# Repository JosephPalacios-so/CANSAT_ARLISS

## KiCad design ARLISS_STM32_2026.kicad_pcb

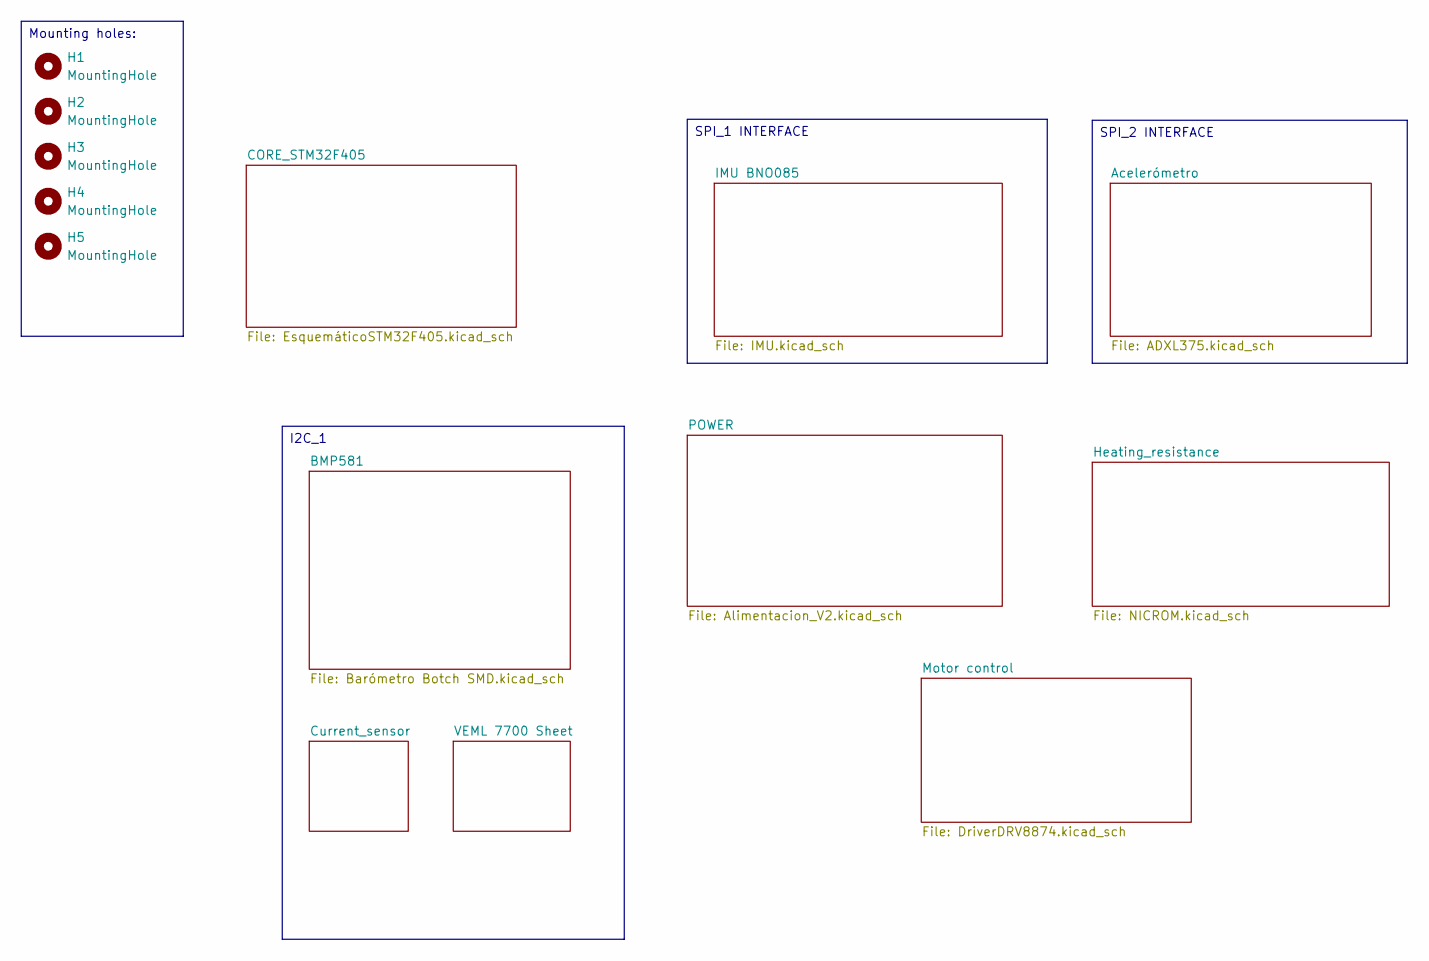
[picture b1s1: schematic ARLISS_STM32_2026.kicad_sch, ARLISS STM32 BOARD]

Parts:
H1, H2, H3, H4, H5: MountingHole; MountingHole_3.2mm_M3_ISO14580_Pad

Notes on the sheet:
SPI_1 INTERFACE
Mounting holes:
SPI_2 INTERFACE
I2C_1

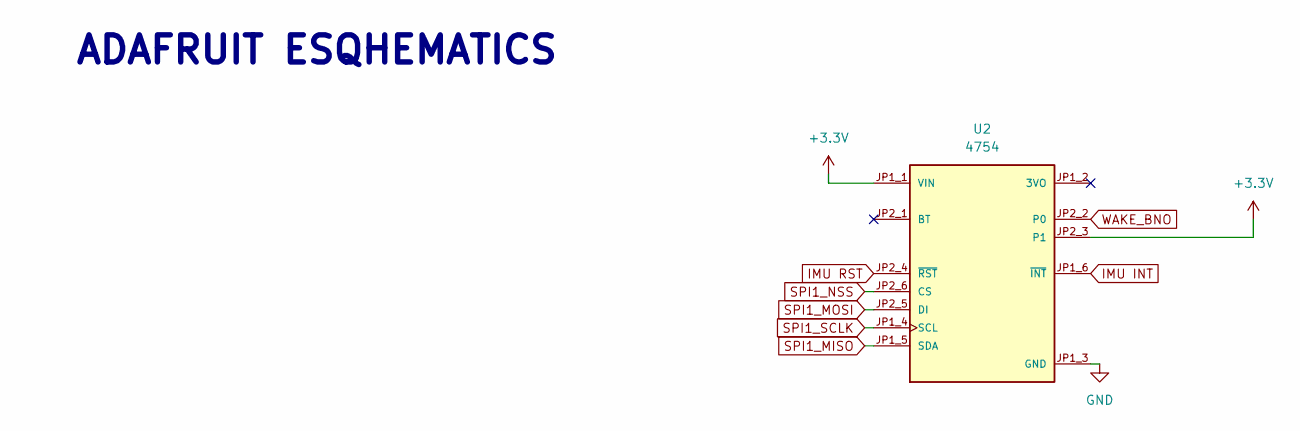
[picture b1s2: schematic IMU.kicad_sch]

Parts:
U2: 4754; MODULE_4754; PARTREV 2021-03-16

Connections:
GND: U2.JP1_3 (GND); also elsewhere on the board
IMU INT: U2.JP1_6 (~INT); also elsewhere on the board
IMU RST: U2.JP2_4 (~RST); also elsewhere on the board
SPI1_MISO: U2.JP1_5 (SDA); also elsewhere on the board
SPI1_MOSI: U2.JP2_5 (DI); also elsewhere on the board
SPI1_NSS: U2.JP2_6 (CS); also elsewhere on the board
SPI1_SCLK: U2.JP1_4 (SCL); also elsewhere on the board
WAKE_BNO: U2.JP2_2 (P0); also elsewhere on the board

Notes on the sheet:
ADAFRUIT ESQHEMATICS

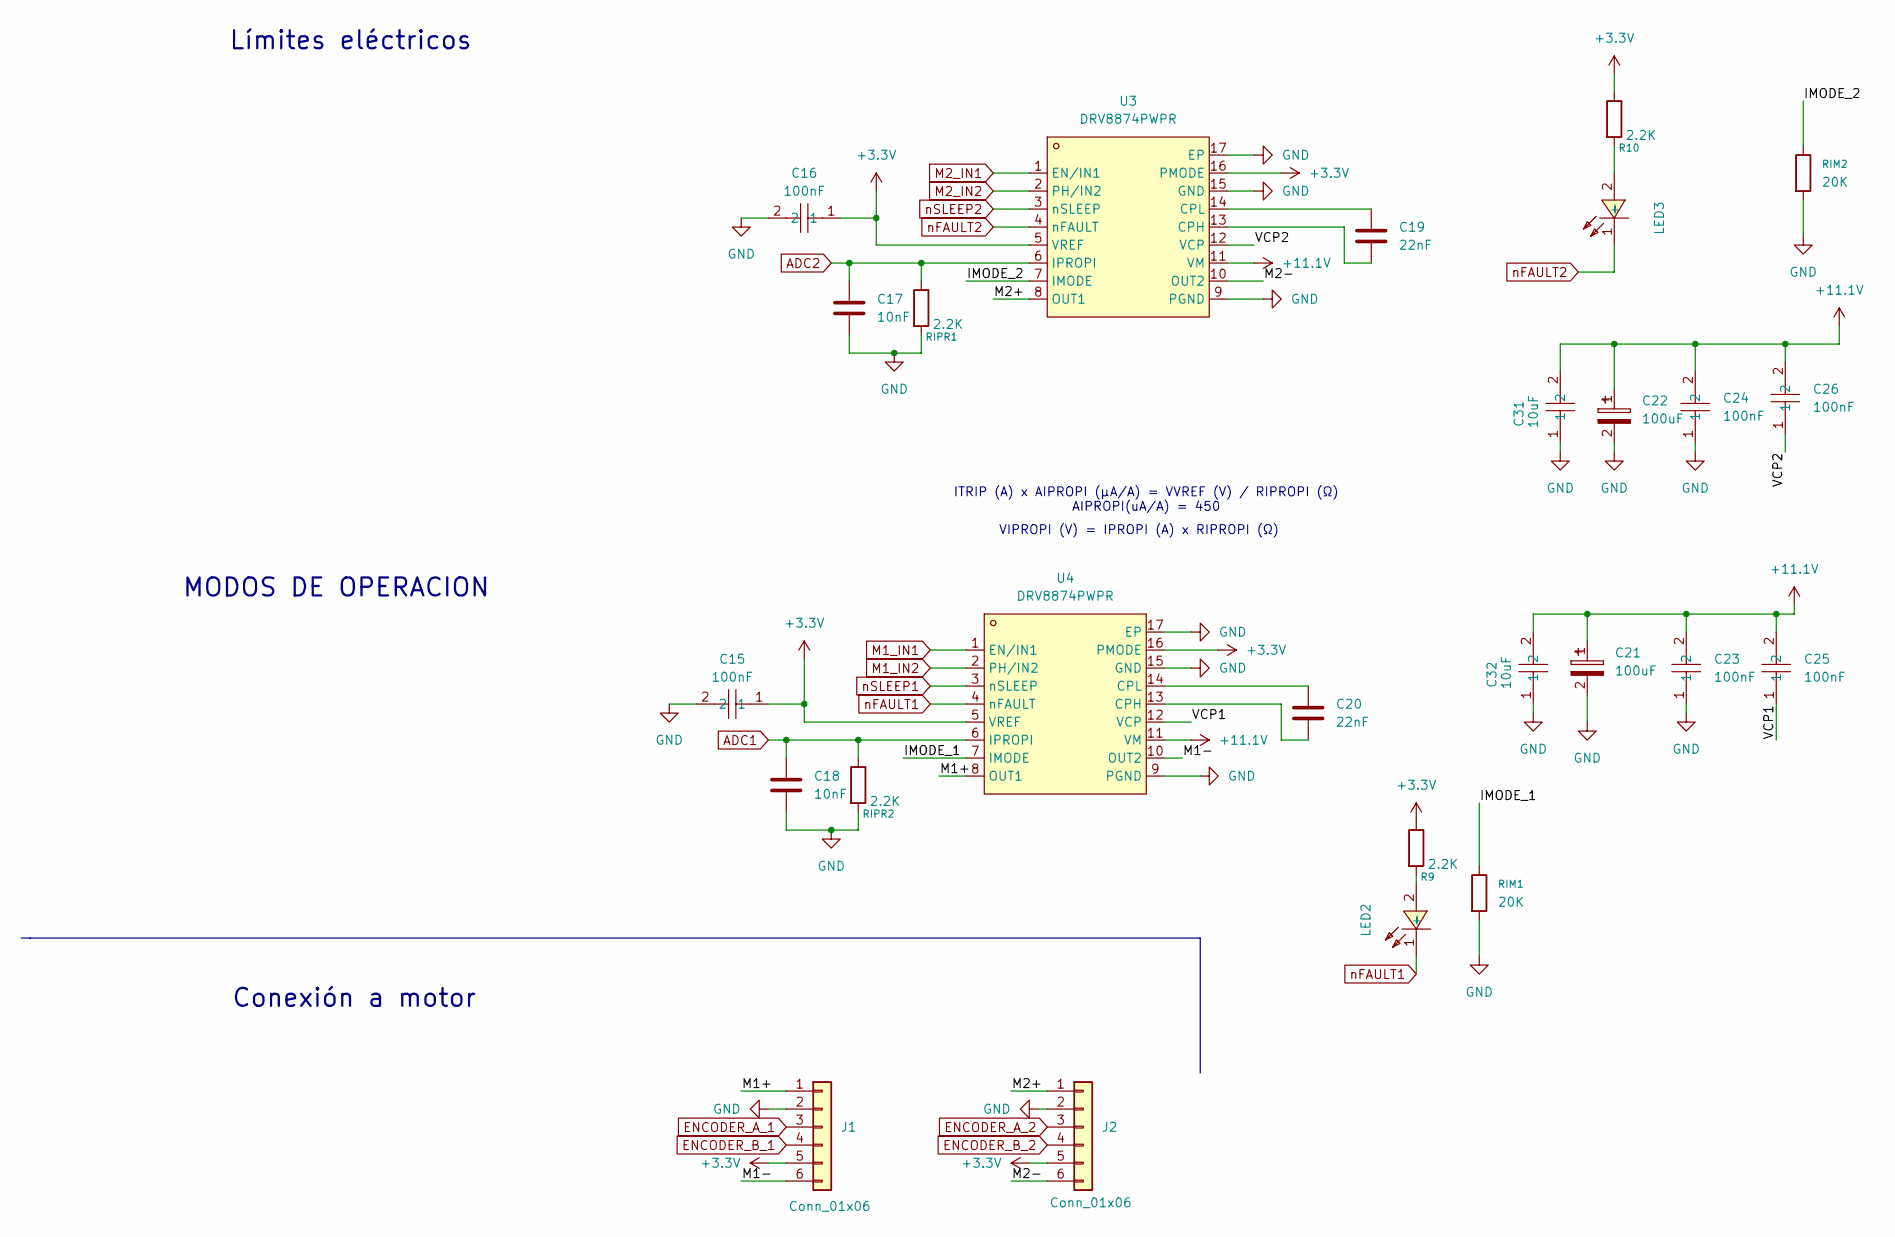
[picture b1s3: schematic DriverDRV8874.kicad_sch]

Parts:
C15, C16, C23, C24, C25, C26: 100nF; C_0603_1608Metric_Pad1.08x0.95mm_HandSolder; MPN TCC0402X7R104J500AT; LCSC Part C282518
C17, C18: 10nF; C_0603_1608Metric_Pad1.08x0.95mm_HandSolder; LCSC C85973
C19, C20: 22nF; C_0603_1608Metric_Pad1.08x0.95mm_HandSolder; LCSC C541460
C21, C22: 100uF; CAP-SMD_BD6.3-L6.6-W6.6-FD; MPN UCM1H101MCL1GS; LCSC Part C729685
C31, C32: 10uF; C_0805_2012Metric_Pad1.18x1.45mm_HandSolder; MPN CL21B106KAYQNNE; LCSC Part C3039694
J1, J2: Conn_01x06; JST_XH_B6B-XH-A_1x06_P2.50mm_Vertical
LED2, LED3: D-R060306L3-KS2; D_0603_1608Metric_Pad1.05x0.95mm_HandSolder; MPN D-060306R1/SS2/L; LCSC Part C118330
R9, R10: 2.2K; R_0603_1608Metric_Pad0.98x0.95mm_HandSolder; LCSC C125931
RIM1, RIM2: 20K; R_0603_1608Metric_Pad0.98x0.95mm_HandSolder; LCSC C7274188
RIPR1, RIPR2: 2.2K; R_0603_1608Metric_Pad0.98x0.95mm_HandSolder; LCSC C125931
U3, U4: DRV8874PWPR; HTSSOP-16_L5.0-W4.4-P0.65-LS6.4-BL-EP; MPN DRV8874PWPR; LCSC Part C1855818

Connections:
+11.1V: C21.1, C22.1, C23.2, C24.2, C25.2, C26.2, C31.2, C32.2, U3.11 (VM), U4.11 (VM); also elsewhere on the board
/Motor control/IMODE_1: RIM1.1, U4.7 (IMODE)
/Motor control/IMODE_2: RIM2.1, U3.7 (IMODE)
/Motor control/M1+: J1.1, U4.8 (OUT1)
/Motor control/M1-: J1.6, U4.10 (OUT2)
/Motor control/M2+: J2.1, U3.8 (OUT1)
/Motor control/M2-: J2.6, U3.10 (OUT2)
/Motor control/VCP1: C25.1, U4.12 (VCP)
/Motor control/VCP2: C26.1, U3.12 (VCP)
ADC1: C18.1, RIPR2.1, U4.6 (IPROPI); also elsewhere on the board
ADC2: C17.1, RIPR1.1, U3.6 (IPROPI); also elsewhere on the board
ENCODER_A_1: J1.3; also elsewhere on the board
ENCODER_A_2: J2.3; also elsewhere on the board
ENCODER_B_1: J1.4; also elsewhere on the board
ENCODER_B_2: J2.4; also elsewhere on the board
GND: C15.2, C16.2, C17.2, C18.2, C21.2, C22.2, C23.1, C24.1, C31.1, C32.1, J1.2, J2.2, RIM1.2, RIM2.2, RIPR1.2, RIPR2.2, U3.9 (PGND), U3.15 (GND), U3.17 (EP), U4.9 (PGND), U4.15 (GND), U4.17 (EP); also elsewhere on the board
M1_IN1: U4.1 (EN/IN1); also elsewhere on the board
M1_IN2: U4.2 (PH/IN2); also elsewhere on the board
M2_IN1: U3.1 (EN/IN1); also elsewhere on the board
M2_IN2: U3.2 (PH/IN2); also elsewhere on the board
unnamed: LED2.2 (+), R9.2
unnamed: LED3.2 (+), R10.2
unnamed: C19.2, U3.13 (CPH)
unnamed: C19.1, U3.14 (CPL)
unnamed: C20.2, U4.13 (CPH)
unnamed: C20.1, U4.14 (CPL)
nFAULT1: LED2.1 (-), U4.4 (nFAULT); also elsewhere on the board
nFAULT2: LED3.1 (-), U3.4 (nFAULT); also elsewhere on the board
nSLEEP1: U4.3 (nSLEEP); also elsewhere on the board
nSLEEP2: U3.3 (nSLEEP); also elsewhere on the board

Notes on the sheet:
Límites eléctricos
MODOS DE OPERACION
VIPROPI (V) = IPROPI (A) x RIPROPI (Ω)
Conexión a motor
ITRIP (A) x AIPROPI (μA/A) = VVREF (V) / RIPROPI (Ω) AIPROPI(uA/A) = 450

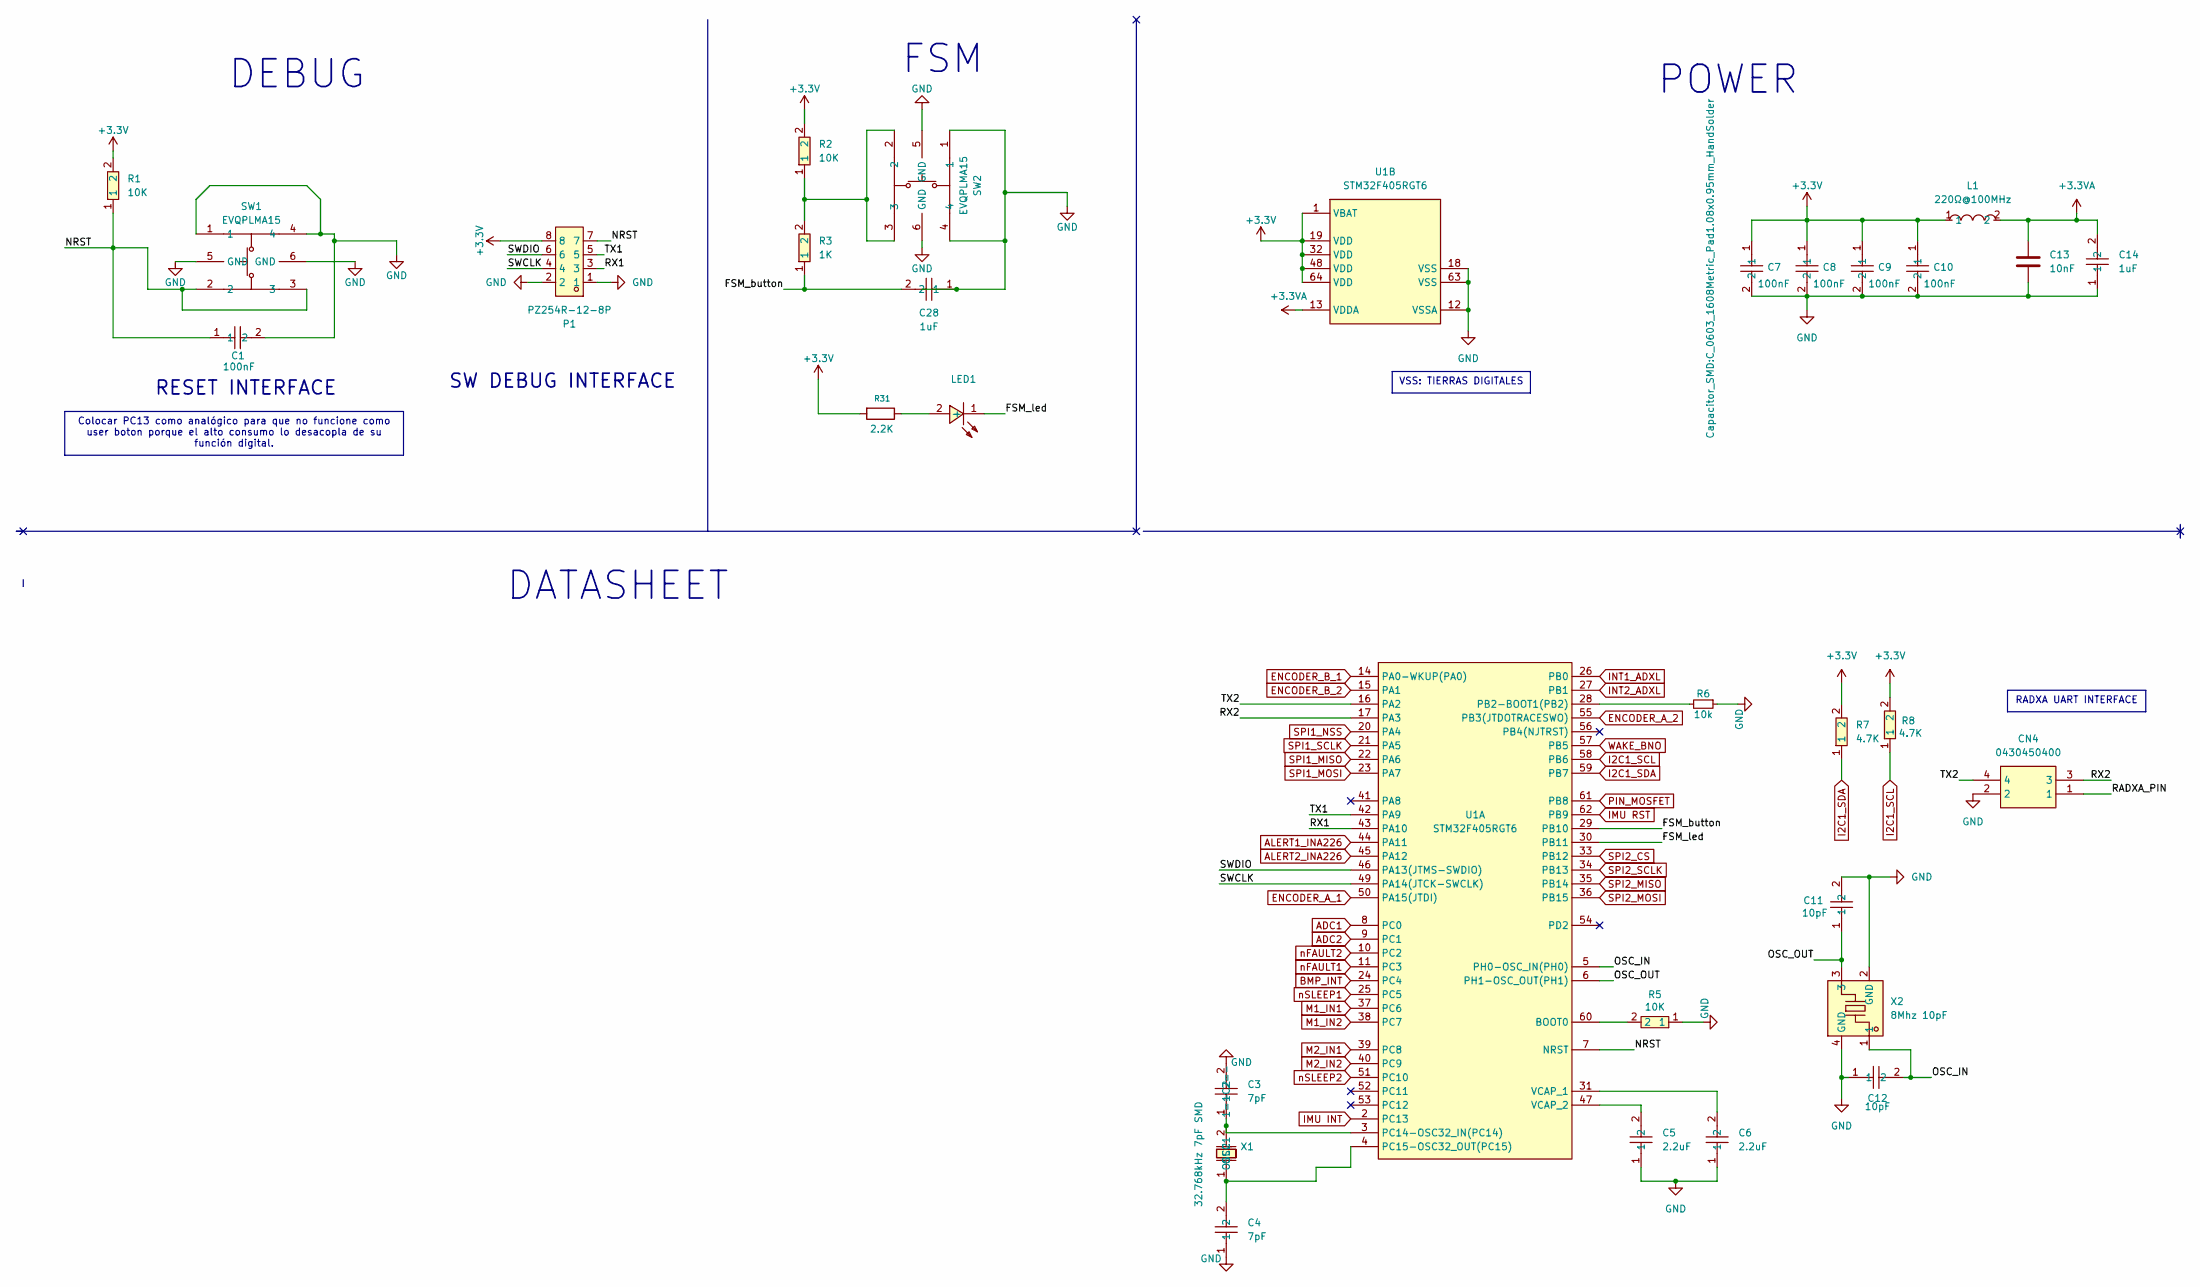
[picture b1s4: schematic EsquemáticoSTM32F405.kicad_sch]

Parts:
C1, C7, C8, C9, C10: 100nF; C_0603_1608Metric_Pad1.08x0.95mm_HandSolder; MPN TCC0402X7R104J500AT; LCSC Part C282518
C3, C4: 7pF; C_0603_1608Metric_Pad1.08x0.95mm_HandSolder; MPN CC0402CRNPO9BN7R0; LCSC Part C519115
C5, C6: 2.2uF; C_0603_1608Metric_Pad1.08x0.95mm_HandSolder; MPN GRM155Z71A225KE44D; LCSC Part C86018
C11, C12: 10pF; C_0603_1608Metric_Pad1.08x0.95mm_HandSolder; MPN CC0402FRNPO9BN100; LCSC Part C309467
C13: 10nF; C_0603_1608Metric_Pad1.08x0.95mm_HandSolder; LCSC C85973
C14, C28: 1uF; C_0603_1608Metric_Pad1.08x0.95mm_HandSolder; MPN CGA0402X5R105K500GT; LCSC Part C559769
CN4: 0430450400; CONN-TH_0430450400; MPN 0430450400; LCSC Part C122413
L1: 220Ω@100MHz; L_0603_1608Metric_Pad1.05x0.95mm_HandSolder; MPN MPZ1608S221ATA00; LCSC Part C76815
LED1: D-R060306L3-KS2; D_0603_1608Metric_Pad1.05x0.95mm_HandSolder; MPN D-060306R1/SS2/L; LCSC Part C118330
P1: PZ254R-12-8P; HDR-TH_8P-P2.54-H-M-R2-C4-S2.54; MPN PZ254R-12-8P; LCSC Part C492432
R1, R2, R5: 10K; R_0603_1608Metric_Pad0.98x0.95mm_HandSolder; MPN RC0603FR-7W10KL; LCSC Part C859110
R3: 1K; R_0603_1608Metric_Pad0.98x0.95mm_HandSolder; MPN RC0603FR-071KL; LCSC Part C22548
R6: 10k; R_0603_1608Metric_Pad0.98x0.95mm_HandSolder; LCSC Part # C25744
R7, R8: 4.7K; R_0603_1608Metric_Pad0.98x0.95mm_HandSolder; MPN RC0603FR-074K7L; LCSC Part C99782
R31: 2.2K; R_0603_1608Metric_Pad0.98x0.95mm_HandSolder; LCSC C114611
SW1, SW2: EVQPLMA15; KEY-SMD_6P-L4.9-4.9-P3.70; MPN EVQPLMA15; LCSC Part C128538
U1: STM32F405RGT6; LQFP-64_L10.0-W10.0-P0.50-LS12.0-BL; MPN STM32F405RGT6; LCSC Part C15742
X1: 32.768kHz 7pF SMD; Crystal_SMD_2012-2Pin_2.0x1.2mm_HandSoldering; MPN X1A0000610006; LCSC Part C99009
X2: 8Mhz 10pF; CRYSTAL-SMD_4P-L3.2-W2.5-BL; MPN XTM32008000GT00351001; LCSC Part C42464264

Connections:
+3.3VA: C13.1, C14.2, L1.2, U1.13 (VDDA)
/CORE_STM32F405/FSM_button: C28.2, R3.1, U1.29 (PB10)
/CORE_STM32F405/FSM_led: LED1.1 (-), U1.30 (PB11)
/CORE_STM32F405/NRST: C1.1, P1.7, R1.1, SW1.2, SW1.3, U1.7 (NRST)
/CORE_STM32F405/OSC_IN: C12.2, U1.5 (PH0-OSC_IN(PH0)), X2.1
/CORE_STM32F405/OSC_OUT: C11.1, U1.6 (PH1-OSC_OUT(PH1)), X2.3
/CORE_STM32F405/RADXA_PIN: CN4.1, U1.54 (PD2)
/CORE_STM32F405/RX1: P1.3, U1.43 (PA10)
/CORE_STM32F405/RX2: CN4.3, U1.17 (PA3)
/CORE_STM32F405/SWCLK: P1.4, U1.49 (PA14(JTCK-SWCLK))
/CORE_STM32F405/SWDIO: P1.6, U1.46 (PA13(JTMS-SWDIO))
/CORE_STM32F405/TX1: P1.5, U1.42 (PA9)
/CORE_STM32F405/TX2: CN4.4, U1.16 (PA2)
ADC1: U1.8 (PC0); also elsewhere on the board
ADC2: U1.9 (PC1); also elsewhere on the board
ALERT1_INA226: U1.44 (PA11); also elsewhere on the board
ALERT2_INA226: U1.45 (PA12); also elsewhere on the board
BMP_INT: U1.24 (PC4); also elsewhere on the board
ENCODER_A_1: U1.50 (PA15(JTDI)); also elsewhere on the board
ENCODER_A_2: U1.55 (PB3(JTDOTRACESWO)); also elsewhere on the board
ENCODER_B_1: U1.14 (PA0-WKUP(PA0)); also elsewhere on the board
ENCODER_B_2: U1.15 (PA1); also elsewhere on the board
GND: C1.2, C3.2, C4.1, C5.1, C6.1, C7.2, C8.2, C9.2, C10.2, C11.2, C12.1, C13.2, C14.1, C28.1, CN4.2, P1.1, P1.2, R5.1, R6.1, SW1.1, SW1.4, SW1.5 (GND), SW1.6 (GND), SW2.1, SW2.4, SW2.5 (GND), SW2.6 (GND), U1.12 (VSSA), U1.18 (VSS), U1.63 (VSS), X2.2 (GND), X2.4 (GND); also elsewhere on the board
I2C1_SCL: R8.1, U1.58 (PB6); also elsewhere on the board
I2C1_SDA: R7.1, U1.59 (PB7); also elsewhere on the board
IMU INT: U1.2 (PC13); also elsewhere on the board
IMU RST: U1.62 (PB9); also elsewhere on the board
INT1_ADXL: U1.26 (PB0); also elsewhere on the board
INT2_ADXL: U1.27 (PB1); also elsewhere on the board
M1_IN1: U1.37 (PC6); also elsewhere on the board
M1_IN2: U1.38 (PC7); also elsewhere on the board
M2_IN1: U1.39 (PC8); also elsewhere on the board
M2_IN2: U1.40 (PC9); also elsewhere on the board
unnamed: LED1.2 (+), R31.1
unnamed: R2.1, R3.2, SW2.2, SW2.3
unnamed: R5.2, U1.60 (BOOT0)
unnamed: R6.2, U1.28 (PB2-BOOT1(PB2))
unnamed: C3.1, U1.3 (PC14-OSC32_IN(PC14)), X1.2 (OSC2)
unnamed: C4.2, U1.4 (PC15-OSC32_OUT(PC15)), X1.1 (OSC1)
unnamed: C6.2, U1.31 (VCAP_1)
unnamed: C5.2, U1.47 (VCAP_2)
PIN_MOSFET: U1.61 (PB8); also elsewhere on the board
SPI1_MISO: U1.22 (PA6); also elsewhere on the board
SPI1_MOSI: U1.23 (PA7); also elsewhere on the board
SPI1_NSS: U1.20 (PA4); also elsewhere on the board
SPI1_SCLK: U1.21 (PA5); also elsewhere on the board
SPI2_CS: U1.33 (PB12); also elsewhere on the board
SPI2_MISO: U1.35 (PB14); also elsewhere on the board
SPI2_MOSI: U1.36 (PB15); also elsewhere on the board
SPI2_SCLK: U1.34 (PB13); also elsewhere on the board
WAKE_BNO: U1.57 (PB5); also elsewhere on the board
nFAULT1: U1.11 (PC3); also elsewhere on the board
nFAULT2: U1.10 (PC2); also elsewhere on the board
nSLEEP1: U1.25 (PC5); also elsewhere on the board
nSLEEP2: U1.51 (PC10); also elsewhere on the board

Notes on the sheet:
RESET INTERFACE
DATASHEET
DEBUG
SW DEBUG INTERFACE
POWER
FSM
Colocar PC13 como analógico para que no funcione como user boton porque el alto consumo lo desacopla de su función digital.
RADXA UART INTERFACE
VSS: TIERRAS DIGITALES

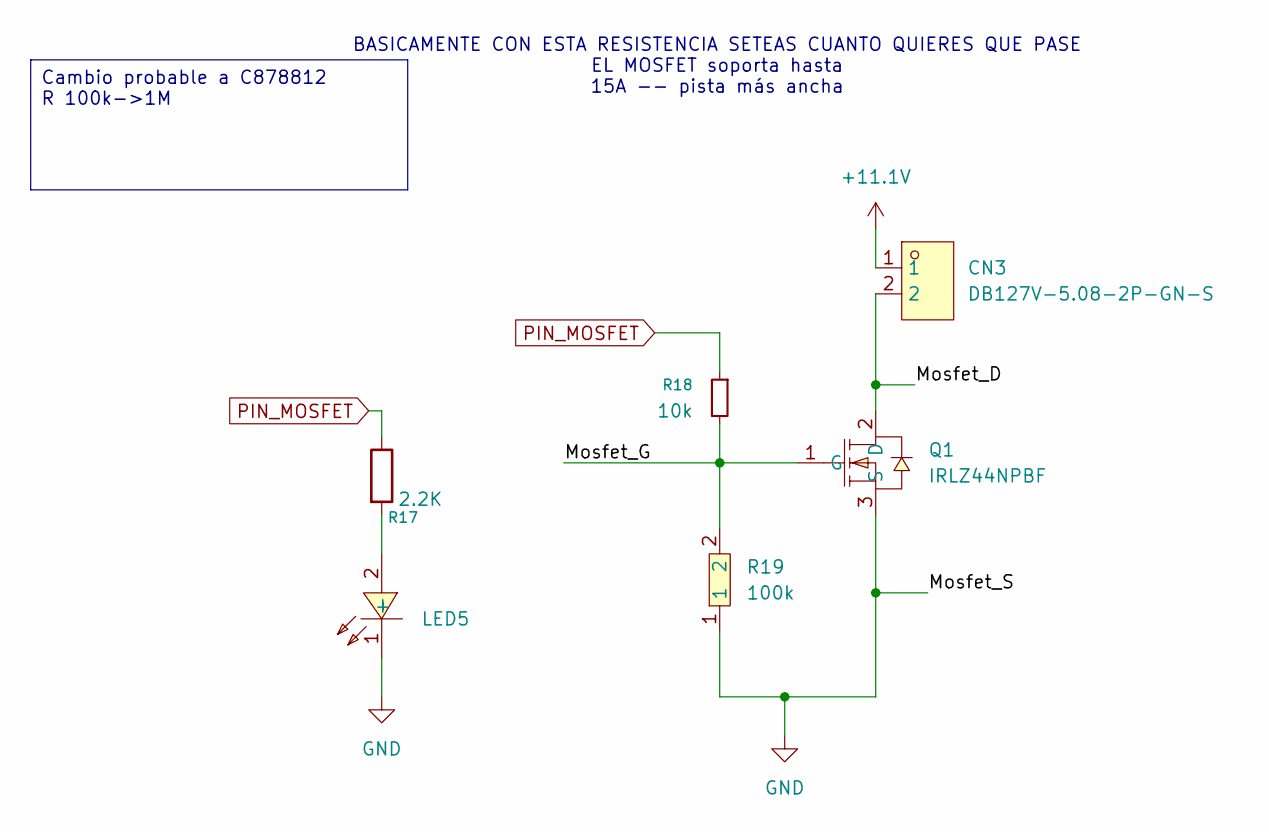
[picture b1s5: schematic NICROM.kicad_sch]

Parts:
CN3: DB127V-5.08-2P-GN-S; CONN-TH_2P-P5.08; MPN DB127V-5.08-2P-GN-S; LCSC Part C3018698
LED5: D-R060306L3-KS2; D_0603_1608Metric_Pad1.05x0.95mm_HandSolder; MPN D-060306R1/SS2/L; LCSC Part C118330
Q1: IRLZ44NPBF; TO-220-3_Horizontal_TabUp; MPN IRLZ44NPBF; LCSC Part C38774
R17: 2.2K; R_0603_1608Metric_Pad0.98x0.95mm_HandSolder; LCSC C114611
R18: 10k; R_0603_1608Metric_Pad0.98x0.95mm_HandSolder
R19: 100k; R_0603_1608Metric_Pad0.98x0.95mm_HandSolder; MPN RC0603FR-07100KL; LCSC Part C14675

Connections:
+11.1V: CN3.1; also elsewhere on the board
/Heating_resistance/Mosfet_D: CN3.2, Q1.2 (D)
/Heating_resistance/Mosfet_G: Q1.1 (G), R18.2, R19.2
GND: LED5.1 (-), Q1.3 (S), R19.1; also elsewhere on the board
unnamed: LED5.2 (+), R17.2
PIN_MOSFET: R17.1, R18.1; also elsewhere on the board

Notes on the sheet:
BASICAMENTE CON ESTA RESISTENCIA SETEAS CUANTO QUIERES QUE PASE EL MOSFET soporta hasta 15A -- pista más ancha
Cambio probable a C878812 R 100k->1M

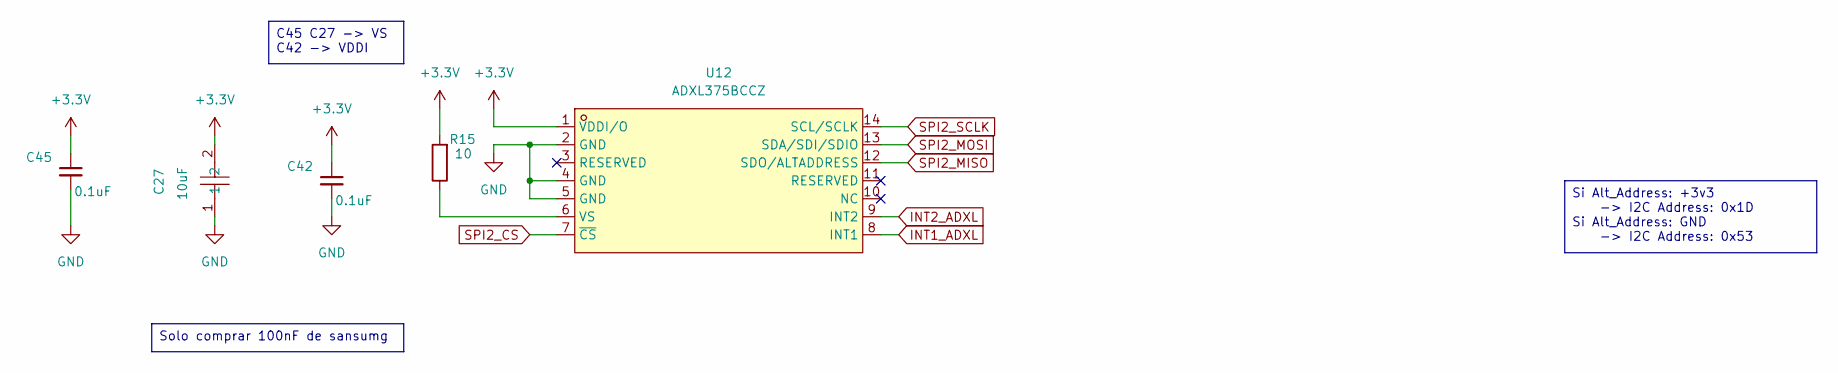
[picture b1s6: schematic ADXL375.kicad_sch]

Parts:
C27: 10uF; C_0805_2012Metric_Pad1.18x1.45mm_HandSolder; MPN CL21B106KAYQNNE; LCSC Part C3039694
C42: 0.1uF; C_0603_1608Metric_Pad1.08x0.95mm_HandSolder
C45: 0.1uF; C_0603_1608Metric
R15: 10; R_0603_1608Metric_Pad0.98x0.95mm_HandSolder
U12: ADXL375BCCZ; LGA-14_L5.0-W3.0-P0.80-BL; LCSC Part C579466

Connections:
GND: C27.1, C42.2, C45.2, U12.2 (GND), U12.4 (GND), U12.5 (GND); also elsewhere on the board
INT1_ADXL: U12.8 (INT1); also elsewhere on the board
INT2_ADXL: U12.9 (INT2); also elsewhere on the board
unnamed: R15.1, U12.6 (VS)
SPI2_CS: U12.7 (~CS); also elsewhere on the board
SPI2_MISO: U12.12 (SDO/ALTADDRESS); also elsewhere on the board
SPI2_MOSI: U12.13 (SDA/SDI/SDIO); also elsewhere on the board
SPI2_SCLK: U12.14 (SCL/SCLK); also elsewhere on the board

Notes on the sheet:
Solo comprar 100nF de sansumg
Si Alt_Address: +3v3 -> I2C Address: 0x1D Si Alt_Address: GND -> I2C Address: 0x53
C45 C27 -> VS C42 -> VDDI

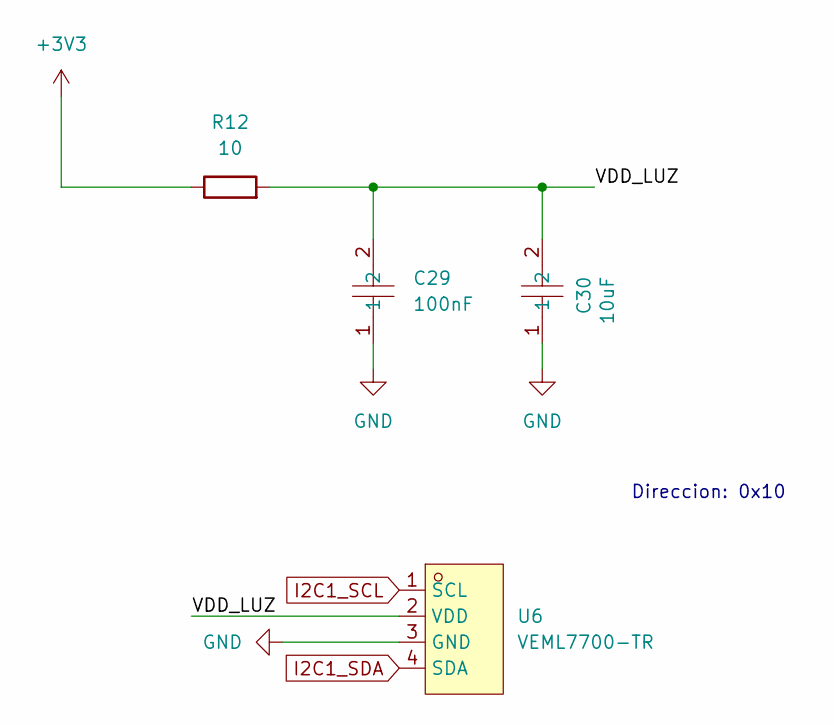
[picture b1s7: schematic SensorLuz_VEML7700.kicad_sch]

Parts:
C29: 100nF; C_0603_1608Metric_Pad1.08x0.95mm_HandSolder; MPN TCC0402X7R104J500AT; LCSC Part C282518
C30: 10uF; C_0805_2012Metric_Pad1.18x1.45mm_HandSolder; MPN CL21B106KAYQNNE; LCSC Part C3039694
R12: 10; R_0603_1608Metric_Pad0.98x0.95mm_HandSolder
U6: VEML7700-TR; LED-SMD_4P-L6.8-W2.4_VEML7700-TR; MPN VEML7700-TR; LCSC Part C504893

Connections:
/VEML 7700 Sheet/VDD_LUZ: C29.2, C30.2, R12.2, U6.2 (VDD)
GND: C29.1, C30.1, U6.3 (GND); also elsewhere on the board
I2C1_SCL: U6.1 (SCL); also elsewhere on the board
I2C1_SDA: U6.4 (SDA); also elsewhere on the board

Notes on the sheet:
Direccion: 0x10

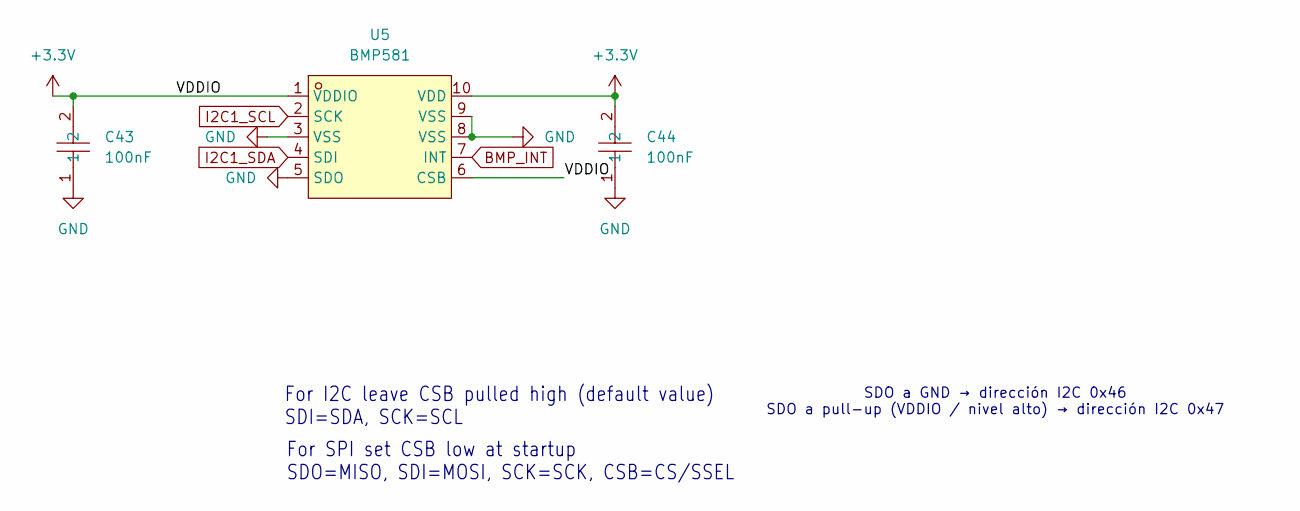
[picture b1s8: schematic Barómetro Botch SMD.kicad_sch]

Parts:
C43, C44: 100nF; C_0603_1608Metric_Pad1.08x0.95mm_HandSolder; MPN TCC0402X7R104J500AT; LCSC Part C282518
U5: BMP581; LGA-10_L2.0-W2.0-P0.50-TL_BMP581; MPN BMP581; LCSC Part C5362283

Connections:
BMP_INT: U5.7 (INT); also elsewhere on the board
GND: C43.1, C44.1, U5.3 (VSS), U5.5 (SDO), U5.8 (VSS), U5.9 (VSS); also elsewhere on the board
I2C1_SCL: U5.2 (SCK); also elsewhere on the board
I2C1_SDA: U5.4 (SDI); also elsewhere on the board

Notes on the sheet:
For I2C leave CSB pulled high (default value) SDI=SDA, SCK=SCL
For SPI set CSB low at startup SDO=MISO, SDI=MOSI, SCK=SCK, CSB=CS/SSEL
SDO a GND → dirección I2C 0x46 SDO a pull-up (VDDIO / nivel alto) → dirección I2C 0x47

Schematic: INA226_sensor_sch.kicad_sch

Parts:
C39, C40: 100nF; C_0603_1608Metric_Pad1.08x0.95mm_HandSolder; MPN TCC0402X7R104J500AT; LCSC Part C282518
C46, C47: 0.1uF; C_0603_1608Metric_Pad1.08x0.95mm_HandSolder
R11: 80mΩ; R_1206_3216Metric_Pad1.30x1.75mm_HandSolder
R20, R21: 4.7K; R_0603_1608Metric_Pad0.98x0.95mm_HandSolder; MPN RC0603FR-074K7L; LCSC Part C99782
R22: 10mΩ; R_2512_6332Metric_Pad1.40x3.35mm_HandSolder
R23, R24, R25, R26: 10; R_0603_1608Metric_Pad0.98x0.95mm_HandSolder
U10, U11: INA226AIDGSR; MSOP-10_L3.0-W3.0-P0.50-LS5.0-BL; MPN INA226AIDGSR; LCSC Part C49851

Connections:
+11.1V: C46.2, R22.2, R24.1, U10.8 (VBUS); also elsewhere on the board
+VDC: C47.2, R11.2, R26.1, U11.8 (VBUS); also elsewhere on the board
+VIN2P: C47.1, R11.1, R25.1; also elsewhere on the board
+VINP: C46.1, R22.1, R23.1; also elsewhere on the board
ALERT1_INA226: R20.1, U10.3 (Alert); also elsewhere on the board
ALERT2_INA226: R21.1, U11.3 (Alert); also elsewhere on the board
GND: C39.1, C40.1, U10.1 (A1), U10.2 (A0), U10.7 (GND), U11.1 (A1), U11.7 (GND); also elsewhere on the board
I2C1_SCL: U10.5 (SCL), U11.5 (SCL); also elsewhere on the board
I2C1_SDA: U10.4 (SDA), U11.4 (SDA); also elsewhere on the board
unnamed: R23.2, U10.10 (VIN+)
unnamed: R24.2, U10.9 (VIN-)
unnamed: R25.2, U11.10 (VIN+)
unnamed: R26.2, U11.9 (VIN-)

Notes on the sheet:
R_shunt = 0.080V / 8A = 10mΩ
R_shunt = 0.080V / 1A = 80mΩ
I2C Address: 0x41
I2C Address: 0x40

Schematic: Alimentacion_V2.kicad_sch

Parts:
C2: 100nF; C_0603_1608Metric_Pad1.08x0.95mm_HandSolder; MPN TCC0402X7R104J500AT; LCSC Part C282518
C33: 10uF; C_0805_2012Metric_Pad1.18x1.45mm_HandSolder; MPN CL21B106KAYQNNE; LCSC Part C3039694
C34, C35: 22uF; C_0805_2012Metric_Pad1.18x1.45mm_HandSolder; MPN C2012X7S1A226MT000E; LCSC Part C342717
CN1, CN2: XT30PW-M; CONN-TH_XT30PW-M; LCSC Part C431092
D1, D2: D_Zener; D_SOD-123
F1: 7A; F1206; MPN LTC1206-1700TS; LCSC Part C52988555
F2: 750mA; F1206; MPN 0466.750NRHF; LCSC Part C187594
L2: 3.3uH; IND-SMD_L4.1-W4.1_FTC404020S; MPN FTC404020S3R3MGCA; LCSC Part C39676071
LED4, LED7: D_0603_1608Metric_Pad1.05x0.95mm_HandSolder; MPN D-060306G1/SS2/G1; LCSC Part C118334
Q2, Q3: AOD4185_C400894; TO-252-3_L6.6-W6.1-P4.57-LS9.9-BR-CW; MPN AOD4185; LCSC Part C400894
R4: 2.2K; R_0603_1608Metric_Pad0.98x0.95mm_HandSolder; LCSC C125931
R16: 10K; R_0603_1608Metric_Pad0.98x0.95mm_HandSolder; MPN RC0603FR-7W10KL; LCSC Part C859110
R32, R33: 100k; R_0603_1608Metric_Pad0.98x0.95mm_HandSolder; MPN RC0603FR-07100KL; LCSC Part C14675
TP1, TP2, TP3, TP4: TestPoint; TestPoint_Pad_D1.5mm
U7: AP63203QWU-7; TSOT-26_L2.9-W1.6-P0.95-LS2.8-BL; MPN AP63203QWU-7; LCSC Part C5248536

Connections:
+11.1V: R16.2, TP2.1 (1_1); also elsewhere on the board
+BATT1: CN2.2 (+), F1.2
+BATT2: CN1.2 (+), F2.2
+VDC: C33.2, U7.2 (EN), U7.3 (VIN); also elsewhere on the board
+VIN2P: D1.1 (K), Q2.3 (S); also elsewhere on the board
+VINP: D2.1 (K), Q3.3 (S); also elsewhere on the board
GND: C33.1, C34.1, C35.1, CN1.1 (-), CN2.1 (-), LED4.1 (-), LED7.1 (-), R32.1, R33.1, TP3.1 (1_1), TP4.1 (1_1), U7.4 (GND); also elsewhere on the board
unnamed: D1.2 (A), Q2.1 (G), R33.2
unnamed: D2.2 (A), Q3.1 (G), R32.2
unnamed: LED4.2 (+), R4.2
unnamed: LED7.2 (+), R16.1
unnamed: F2.1, Q2.2 (D)
unnamed: F1.1, Q3.2 (D)
unnamed: C2.2, U7.6 (BST)
unnamed: C2.1, L2.1, U7.5 (SW)

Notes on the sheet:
BATT_11.1V
BATT_7.4V
Reverse polarity + fusible

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
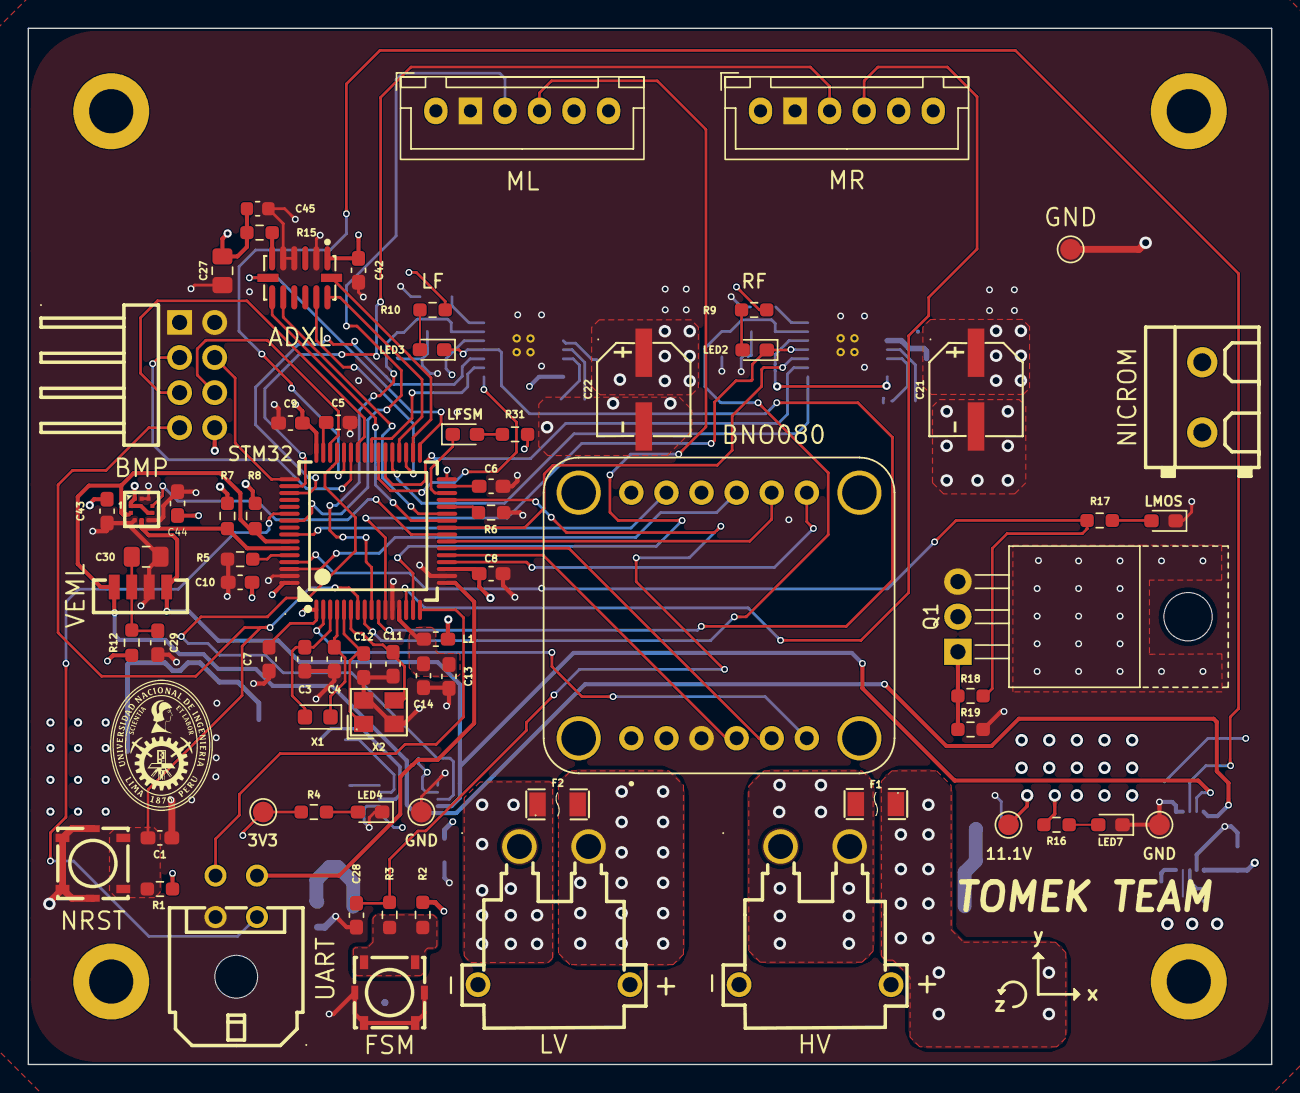
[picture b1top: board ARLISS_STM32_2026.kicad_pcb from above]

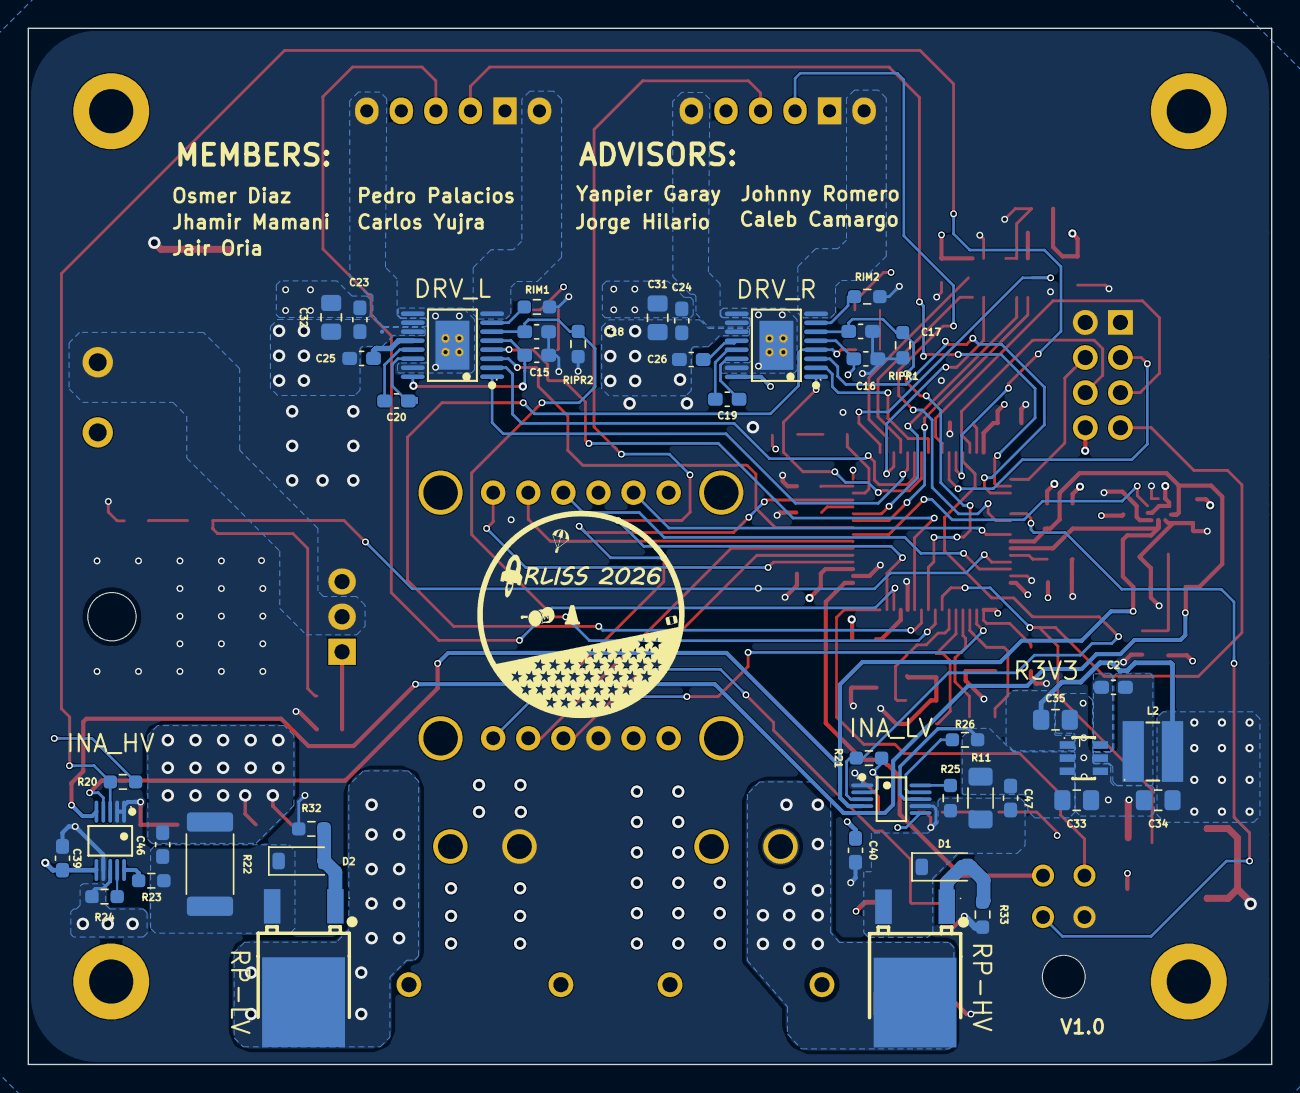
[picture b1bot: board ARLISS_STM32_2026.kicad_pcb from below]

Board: 4 copper layers, 90.0 x 75.0 mm, 119 parts (44 on the bottom side), 93 nets.

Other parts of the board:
TP4#2: TestPoint; TestPoint_Pad_D1.5mm

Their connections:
GND: TP4#2.1 (1_1); also elsewhere on the board

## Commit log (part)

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2026-05-18 First version - ARLISS STM32 2026
2026-05-19 qa! qa! vm
2026-05-21 21/05
2026-05-22 22/05
2026-05-23 Mejoras hasta sábado
2026-05-23 STM32 mapeo
2026-05-23 Avances antes de merge
2026-05-25 STM32 actualización 25/03
2026-05-26 AVANCE STM32
2026-05-28 Protocolos I2C/SPI
2026-05-28 INA SENSOR
2026-05-29 Todo menos alimentación
2026-05-30 ALIMENTACIÓN
2026-06-01 Esquemático V1
2026-06-06 BECERRA
2026-06-06 AVANCE 06
2026-06-07 Test 00 final
2026-06-07 Parte 01 07/06
2026-06-07 feat: [solución de rules checker]
2026-06-07 RULE CHECKER OK
2026-06-09 Errores del esquematico solucionados
2026-06-09 FOOTPRINTS V1
2026-06-09 Footprints V2
2026-06-09 Actualizacion previo al ingreso de la rama ARLISS
2026-06-14 Actualización de nets
2026-06-14 Cantidad de errores en la PCB: 29
2026-06-14 Cantidad de errores de la placa: 05
2026-06-14 Cantidad de errores en la placa: 04
2026-06-14 Esquemático Versión mejorada
2026-06-15 PCB ordenada V1
2026-06-17 Alimentacion ordenado
2026-06-17 DPS ORDENADO
2026-06-18 Driver Ordenado
2026-06-18 PCB_orden
2026-06-20 Primer Ruteo de PCB
2026-06-21 Arreglos de esquemático
2026-06-22 Arreglando footprints
2026-06-23 all before traces
2026-06-25 Todo antes de PCB
